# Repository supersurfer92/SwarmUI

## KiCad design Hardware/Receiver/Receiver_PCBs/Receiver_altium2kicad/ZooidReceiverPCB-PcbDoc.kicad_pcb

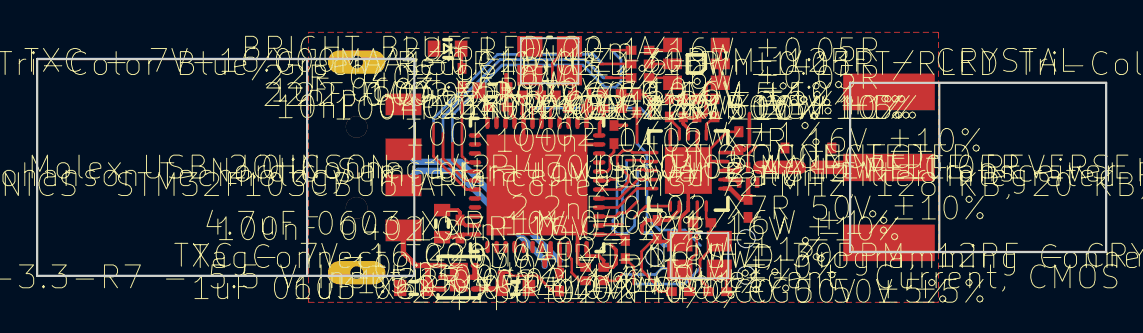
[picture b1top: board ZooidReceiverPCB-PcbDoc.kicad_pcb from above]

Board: 4 copper layers, 59.4 x 13.3 mm, 45 parts (1 on the bottom side), 37 nets.

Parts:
A1: 142-4701-801
B1: 2.45 GHz Impedance Matched Balun-Filter: Optimize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; 2450BM14A0002
C1, C4, C5, C6, C7, C8, C9, C12, C13, C14, C15, C16, C17, C18, C19: Chip Body 1.0 x 0.5 mm (LxW typ); 0402
C2, C3, C10, C11: Chip Body 1.6 x 0.8 mm (LxW typ); 0603
D1: 3.5 x 2.8 mm 6-SMD Flat Leads; 3.5x2.8 mm 6-SMD
D2: Chip Body 1.6 x 0.8 mm (LxW typ); 0603 - LED
J1: Molex 48037-2200 USB Type A Receptacle; 48037-2200
P1: TagConnector TC2030-IDC-NL; TC2030-IDC-NL
R1, R2, R3, R4, R5, R6, R7, R8, R9, R10, R13, R14, R15: Chip Body 1.0 x 0.5 mm (LxW typ); 0402
R11, R12: Chip Body 1.0 x 0.5 mm (LxW typ); 0402 - NOBODY
U1: QFN, 48-Leads, Body 7,00x7,00mm, Pitch 0,50mm, Th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; QFN50P700X700X60_HS-49L
U2: . 6-Lead Lead Frame Chip Scale Package [LFCSP_UD]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; LFCSP-6 2.0X2.0X0.55
U3: QFN, 20-Leads, Body 4,00x4,00mm, Pitch 0,50mm, Th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; QFN50P400X400X95_HS-21L
Y1, Y2: 3.2x2.5 CRYSTAL

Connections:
+3.3V: C1.2, C2.2, C3.2, C4.2, C5.2, C6.2, C11.2, C12.2, C13.2, C14.2, C15.2, D1.1, D1.2, D1.3, D2.1, P1.1, R5.2, R15.2, U1.1, U1.9, U1.24, U1.36, U1.48, U2.1, U3.7, U3.15, U3.18
ANT1: B1.4, U3.12
ANT2: B1.3, U3.13
GND: A1.2, B1.2, C1.1, C2.1, C3.1, C4.1, C5.1, C6.1, C7.1, C8.1, C9.1, C10.1, C11.1, C12.1, C13.1, C14.1, C15.1, C16.1, C17.1, C18.1, C19.1, J1.4, J1.5, P1.5, R4.1, R11.1, R12.1, R13.1, U1.8, U1.23, U1.35, U1.47, U1.49, U2.2, U2.3, U2.5, U2.7, U3.8, U3.14, U3.17, U3.20, U3.21, Y1.2, Y1.4, Y2.2, Y2.4
MCU_X1_16MHZ: C8.2, U1.5, Y1.1
MCU_X2_16MHZ: C9.2, U1.6, Y1.3
NRST: C7.2, R2.1, R5.1, U1.7
NetA1_1: A1.1, R10.2, R12.2
NetB1_1: B1.1, R10.1, R11.2
NetC17_2: C17.2, U3.19
NetD1_4: D1.4, R6.2
NetD1_5: D1.5, R7.2
NetD1_6: D1.6, R8.2
NetD2_2: D2.2, R9.2
NetP1_2: P1.2, R1.2
NetP1_3: P1.3, R2.2
NetP1_4: P1.4, R3.2
NetR4_2: R4.2, U1.44
NetR13_2: R13.2, U3.16
RADIO_SPI.CE: U1.42, U3.1
RADIO_SPI.CSN: U1.38, U3.2
RADIO_SPI.IRQ: U1.43, U3.6
RADIO_SPI.MISO: U1.40, U3.5
RADIO_SPI.MOSI: U1.41, U3.4
RADIO_SPI.SCK: U1.39, U3.3
RADIO_X1_16MHZ: C18.2, R14.1, U3.10, Y2.3
RADIO_X2_16MHZ: C19.2, R14.2, U3.9, Y2.1
RGBLED1: R7.1, U1.19
RGBLED2: R6.1, U1.17
RGBLED3: R8.1, U1.18
STATUS_LED: R9.1, U1.16
SWCLK: R3.1, U1.37
SWDIO: R1.1, U1.34
USB_D_N: J1.2, U1.32
USB_D_P: J1.3, R15.1, U1.33
VDD_PA: B1.5, C16.2, U3.11
VUSB: C10.2, J1.1, U2.4, U2.6

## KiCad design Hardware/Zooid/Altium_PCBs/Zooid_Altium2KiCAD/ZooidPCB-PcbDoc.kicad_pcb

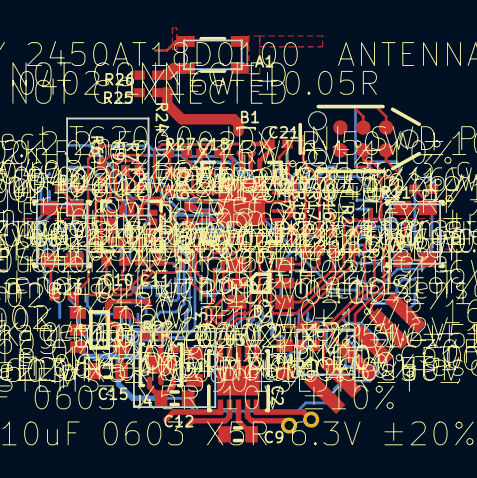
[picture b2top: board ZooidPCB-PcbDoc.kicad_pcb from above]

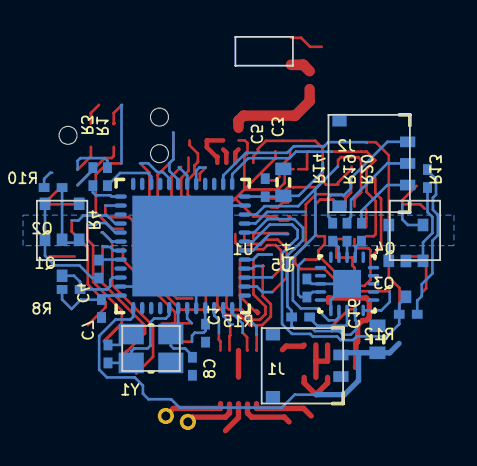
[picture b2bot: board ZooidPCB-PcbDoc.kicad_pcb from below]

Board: 4 copper layers, 22.4 x 20.4 mm, 70 parts (29 on the bottom side), 59 nets.

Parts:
A1: ANTENNA CHIP 2.4GHZ; 2450AT18D0100
C1, C4, C5, C6, C7, C8, C10, C11, C14, C17, C18, C19, C20, C21, C22: Chip Body 1.0 x 0.5 mm (LxW typ); 0402
C2, C3, C9, C12, C13, C15, C16: Chip Body 1.6 x 0.8 mm (LxW typ); 0603
D1, D3: Silicon PIN Photodiode; PD15-22C/TR8
D2: 3.5 x 2.8 mm 6-SMD Flat Leads; 3.5X2.8 MM 6-SMD
J1: 78171-0002
J2: 78171-0003
P1: TagConnector TC2030-IDC-NL; TC2030-IDC-NL
P2: HEADER 2X1 0.05
P5: EXTENSION_PORT
Q1, Q2, Q3, Q4: SOT23, 3-Leads, Body 2.9x1.3mm, Pitch 0.95mm, Lea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; SOT23_L
R1, R2, R3, R4, R5, R6, R7, R8, R9, R10, R11, R12, R13, R14, R15, R16, R17, R18, R19, R20, R21, R22, R23, R24, R27: Chip Body 1.0 x 0.5 mm (LxW typ); 0402
R25, R26: Chip Body 1.0 x 0.5 mm (LxW typ); 0402 - NOBODY
U1: QFN, 48-Leads, Body 7,00x7,00mm, Pitch 0,50mm, Th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; QFN50P700X700X60_HS-49L
U2: LGA, 14-Leads, Body 3.00x2.50mm, Pitch 0.50mm, IP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; LGA-14 2.5X3X0.86 MM 14L
U3: DFN50P300X300X75_HS-11N
U4: . 6-Lead Lead Frame Chip Scale Package [LFCSP_UD]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; LFCSP-6 2.0X2.0X0.55
U5: QFN, 20-Leads, Body 3.00x3.00mm, Pitch 0.45mm, Th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; QFN45P300X300X85_HS-21L
U6: SOT23, 5-Leads, Body 2.9x1.6mm, Pitch 0.95mm, Lea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; SOT-23-OT5_L
U7: QFN, 20-Leads, Body 4,00x4,00mm, Pitch 0,50mm, Th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; QFN50P400X400X95_HS-21L
Y1: 3.2X2.5 CRYSTAL

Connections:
+3.3V: C1.2, C2.2, C3.2, C4.2, C5.2, C9.2, C10.2, C11.2, C13.2, C14.2, C17.2, C18.2, C19.2, C20.2, D1.2, D2.1, D2.2, D2.3, D3.2, P1.1, P5.1, R5.2, R6.2, R7.2, R8.2, R9.2, R10.2, R12.2, R13.2, R15.2, R23.2, U1.9, U1.24, U1.48, U2.5, U2.8, U2.12, U3.8, U4.1, U5.9, U5.13, U7.7, U7.15, U7.18
CHARGING: R23.1, U1.26, U6.1
GND: A1.2, C1.1, C2.1, C3.1, C4.1, C5.1, C6.1, C7.1, C8.1, C9.1, C10.1, C11.1, C12.1, C13.1, C14.1, C15.1, C16.1, C17.1, C18.1, C19.1, C20.1, C21.1, C22.1, J1.2, P1.5, P5.6, Q1.2, Q2.2, Q3.2, Q4.2, R4.1, R11.1, R21.1, R22.2, R25.1, R26.1, R27.1, U1.8, U1.23, U1.47, U1.49, U2.1, U2.2, U2.3, U2.6, U2.7, U3.3, U3.11, U4.2, U4.3, U4.5, U4.7, U5.8, U5.11, U5.21, U6.2, U7.8, U7.14, U7.17, U7.20, U7.21, Y1.2, Y1.4
I2C.SCL: R9.1, U1.21, U2.13, U5.15
I2C.SDA: R7.1, U1.22, U2.14, U5.12
I2C_EXT.SCL: P5.5, U1.42
I2C_EXT.SDA: P5.4, U1.43
IMU_INT: R6.1, U1.25, U2.4
IO1: P5.2, U1.40
IO2: P5.3, U1.41
MCU_X1_16MHZ: C7.2, U1.5, Y1.1
MCU_X2_16MHZ: C8.2, U1.6, Y1.3
MOTOR_CONTROL1: U1.10, U3.1
MOTOR_CONTROL2: U1.11, U3.2
MOTOR_CONTROL3: U1.12, U3.4
MOTOR_CONTROL4: U1.13, U3.5
NRST: C6.2, R2.1, R5.1, U1.7
NetA1_1: A1.1, R24.2, R26.2
NetB1_1: R24.1, R25.2
NetC15_2: C15.2, U6.4
NetC22_2: C22.2, U7.19
NetD1_1: D1.1, Q2.1, R11.2
NetD2_4: D2.4, R16.2
NetD2_5: D2.5, R17.2
NetD2_6: D2.6, R18.2
NetD3_1: D3.1, Q4.1, R21.2
NetJ2_1: J2.1, R14.2
NetJ2_2: J2.2, R19.2
NetJ2_3: J2.3, R20.2
NetP1_2: P1.2, R1.2
NetP1_3: P1.3, R2.2
NetP1_4: P1.4, R3.2
NetP2_1: P2.1, U3.10
NetP2_2: P2.2, U3.9
NetQ1_1: Q1.1, Q2.3, R10.1
NetQ3_1: Q3.1, Q4.3, R13.1
NetR4_2: R4.2, U1.44
NetR14_1: R14.1, U5.4
NetR19_1: R19.1, U5.3
NetR20_1: R20.1, U5.2
NetR22_1: R22.1, U6.5
NetR27_2: R27.2, U7.16
PHOTODIODE_1: Q1.3, R8.1, U1.46
PHOTODIODE_2: Q3.3, R12.1, U1.19
RADIO_CE: U1.18, U7.1
RADIO_CLK: U1.29, U7.10
RADIO_IRQ: U1.38, U7.6
RADIO_SPI.CSN: U1.14, U7.2
RADIO_SPI.MISO: U1.16, U7.5
RADIO_SPI.MOSI: U1.17, U7.4
RADIO_SPI.SCK: U1.15, U7.3
RGBLED1: R17.1, U1.31
RGBLED2: R16.1, U1.32
RGBLED3: R18.1, U1.30
SWCLK: R3.1, U1.37
SWDIO: R1.1, U1.34
TOUCH_CHG: R15.1, U1.20, U5.14
VBAT: C12.2, C16.2, J1.1, U1.1, U4.4, U4.6, U6.3
VDD_PA: C21.2, U7.11
